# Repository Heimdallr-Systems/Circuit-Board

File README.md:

# Circuit-Board

Custom Power and IO board for the robot

## Folders

### CapsoneParts.3dshapes

Custom 3D models for KiCAD

### CapsstoneParts.pretty

Custom footprints for KiCAD

### optionalParts

Schematics of circuits that might be added to the main PCB

### Simulations/TINA-TI

[TINA-TI](https://www.ti.com/tool/TINA-TI) simulations used during design

### Simulations/LTspice

[LTspice](https://www.analog.com/en/design-center/design-tools-and-calculators/ltspice-simulator.html) simulations used
during design process

### TPS55288RPMR

Files used to make the TPS55288 components for KiCAD

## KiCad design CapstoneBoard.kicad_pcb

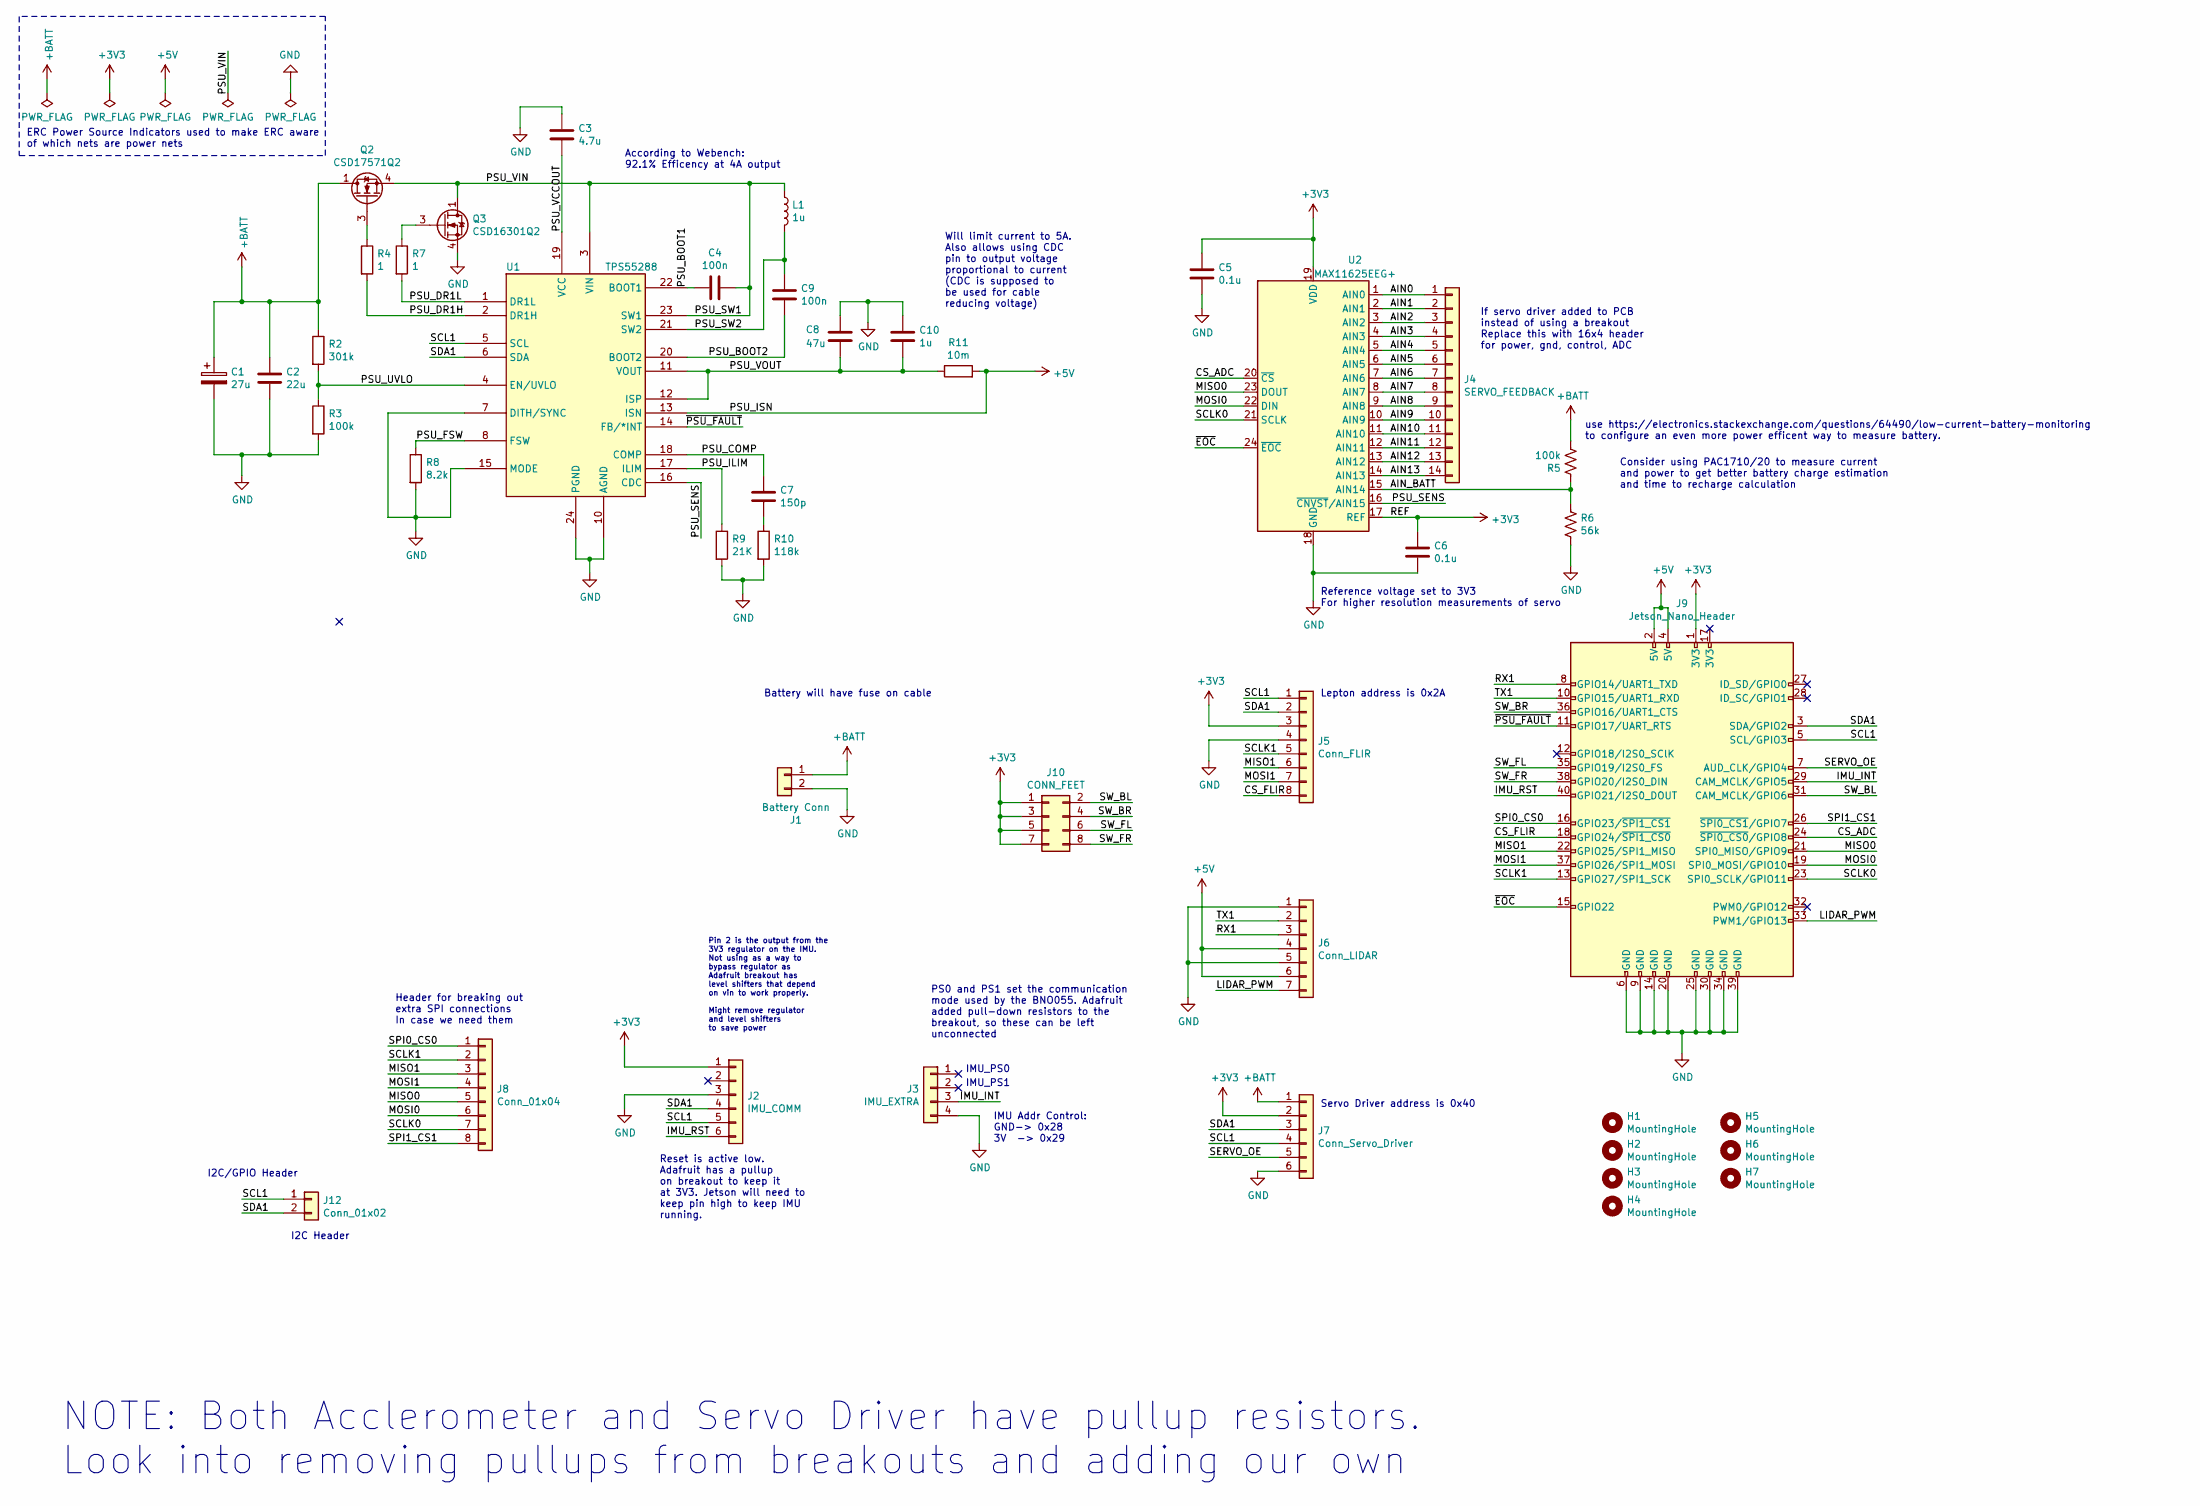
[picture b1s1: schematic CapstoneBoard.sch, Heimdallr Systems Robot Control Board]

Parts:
C1: 27u; C_1206_3216Metric_Pad1.33x1.80mm_HandSolder
C2: 22u; C_1206_3216Metric_Pad1.33x1.80mm_HandSolder
C3: 4.7u; C_1206_3216Metric_Pad1.33x1.80mm_HandSolder
C4, C9: 100n; C_1206_3216Metric_Pad1.33x1.80mm_HandSolder
C5, C6: 0.1u; C_0805_2012Metric_Pad1.18x1.45mm_HandSolder
C7: 150p; C_1206_3216Metric_Pad1.33x1.80mm_HandSolder
C8: 47u; C_1206_3216Metric_Pad1.33x1.80mm_HandSolder
C10: 1u; C_1206_3216Metric_Pad1.33x1.80mm_HandSolder
H1, H2, H3, H4, H5, H6, H7: MountingHole; MountingHole_2.5mm_Pad
J1: Battery Conn; wireConn2
J2: IMU_COMM; PinSocket_1x06_P2.54mm_Vertical
J3: IMU_EXTRA; PinSocket_1x04_P2.54mm_Vertical
J4: SERVO_FEEDBACK; PinHeader_1x14_P2.54mm_Vertical
J5: Conn_FLIR; PinHeader_1x08_P2.54mm_Vertical
J6: Conn_LIDAR; PinHeader_1x07_P2.54mm_Vertical
J7: Conn_Servo_Driver; PinHeader_1x06_P2.54mm_Vertical
J8: Conn_01x04; PinHeader_1x08_P2.54mm_Vertical
J9: Jetson_Nano_Header; PinHeader_2x20_P2.54mm_Vertical
J10: CONN_FEET; PinHeader_2x04_P2.54mm_Vertical
J12: Conn_01x02; PinHeader_1x02_P2.54mm_Vertical
L1: 1u; L_Vishay_IHLP-1212
Q2: CSD17571Q2; Texas_DQK
Q3: CSD16301Q2; Texas_DQK
R2: 301k; R_1206_3216Metric_Pad1.30x1.75mm_HandSolder
R3, R5: 100k; R_1206_3216Metric_Pad1.30x1.75mm_HandSolder
R4, R7: 1; R_1206_3216Metric_Pad1.30x1.75mm_HandSolder
R6: 56k; R_1206_3216Metric_Pad1.30x1.75mm_HandSolder
R8: 8.2k; R_1206_3216Metric_Pad1.30x1.75mm_HandSolder
R9: 21K; R_1206_3216Metric_Pad1.30x1.75mm_HandSolder
R10: 118k; R_1206_3216Metric_Pad1.30x1.75mm_HandSolder
R11: 10m; R_1206_3216Metric_Pad1.30x1.75mm_HandSolder
U1: TPS55288; VQFN-HR-26
U2: MAX11625EEG+; QSOP-24_3.9x8.7mm_P0.635mm

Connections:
+3V3: C5.1, C6.1, J2.1, J5.3, J7.2, J9.1 (3V3), J10.1, J10.3, J10.5, J10.7, U2.17 (REF), U2.19 (VDD)
+5V: J6.4, J6.6, J9.2 (5V), J9.4 (5V), R11.2, U1.13 (ISN)
+BATT: C1.1, C2.1, J1.1, J7.1, Q2.1 (D), Q2.2 (D), Q2.5 (D), Q2.6 (D), Q2.8 (D), R2.1, R5.2
/AIN0: J4.1, U2.1 (AIN0)
/AIN1: J4.2, U2.2 (AIN1)
/AIN2: J4.3, U2.3 (AIN2)
/AIN3: J4.4, U2.4 (AIN3)
/AIN4: J4.5, U2.5 (AIN4)
/AIN5: J4.6, U2.6 (AIN5)
/AIN6: J4.7, U2.7 (AIN6)
/AIN7: J4.8, U2.8 (AIN7)
/AIN8: J4.9, U2.9 (AIN8)
/AIN9: J4.10, U2.10 (AIN9)
/AIN10: J4.11, U2.11 (AIN10)
/AIN11: J4.12, U2.12 (AIN11)
/AIN12: J4.13, U2.13 (AIN12)
/AIN13: J4.14, U2.14 (AIN13)
/AIN_BATT: R5.1, R6.1, U2.15 (AIN14)
/CS_ADC: J9.24 (~SPI0_CS0~/GPIO8), U2.20 (~CS)
/CS_FLIR: J5.8, J9.18 (GPIO24/~SPI1_CS0~)
/IMU_INT: J3.3, J9.29 (CAM_MCLK/GPIO5)
/IMU_RST: J2.6, J9.40 (GPIO21/I2S0_DOUT)
/LIDAR_PWM: J6.7, J9.33 (PWM1/GPIO13)
/MISO0: J8.5, J9.21 (SPI0_MISO/GPIO9), U2.23 (DOUT)
/MISO1: J5.6, J8.3, J9.22 (GPIO25/SPI1_MISO)
/MOSI0: J8.6, J9.19 (SPI0_MOSI/GPIO10), U2.22 (DIN)
/MOSI1: J5.7, J8.4, J9.37 (GPIO26/SPI1_MOSI)
/PSU_BOOT1: C4.2, U1.22 (BOOT1)
/PSU_BOOT2: C9.1, U1.20 (BOOT2)
/PSU_COMP: C7.1, U1.18 (COMP)
/PSU_DR1H: R4.2, U1.2 (DR1H)
/PSU_DR1L: R7.2, U1.1 (DR1L)
/PSU_FSW: R8.1, U1.8 (FSW)
/PSU_ILIM: R9.1, U1.17 (ILIM)
/PSU_SENS: U1.16 (CDC), U2.16 (~CNVST~/AIN15)
/PSU_SW1: C4.1, L1.1, Q2.4 (S), Q2.7 (S), Q3.1 (D), Q3.2 (D), Q3.5 (D), Q3.6 (D), Q3.8 (D), U1.3 (VIN), U1.23 (SW1)
/PSU_SW2: C9.2, L1.2, U1.21 (SW2), U1.25 (SW2)
/PSU_UVLO: R2.2, R3.1, U1.4 (EN/UVLO)
/PSU_VCCOUT: C3.2, U1.19 (VCC)
/PSU_VOUT: C8.2, C10.2, R11.1, U1.11 (VOUT), U1.12 (ISP), U1.26 (VOUT)
/RX1: J6.3, J9.8 (GPIO14/UART1_TXD)
/SCL1: J2.5, J5.1, J7.4, J9.5 (SCL/GPIO3), J12.1, U1.5 (SCL)
/SCLK0: J8.7, J9.23 (SPI0_SCLK/GPIO11), U2.21 (SCLK)
/SCLK1: J5.5, J8.2, J9.13 (GPIO27/SPI1_SCK)
/SDA1: J2.4, J5.2, J7.3, J9.3 (SDA/GPIO2), J12.2, U1.6 (SDA)
/SERVO_OE: J7.5, J9.7 (AUD_CLK/GPIO4)
/SPI0_CS0: J8.1, J9.16 (GPIO23/~SPI1_CS1~)
/SPI1_CS1: J8.8, J9.26 (~SPI0_CS1~/GPIO7)
/SW_BL: J9.31 (CAM_MCLK/GPIO6), J10.2
/SW_BR: J9.36 (GPIO16/UART1_CTS), J10.4
/SW_FL: J9.35 (GPIO19/I2S0_FS), J10.6
/SW_FR: J9.38 (GPIO20/I2S0_DIN), J10.8
/TX1: J6.2, J9.10 (GPIO15/UART1_RXD)
/~EOC~: J9.15 (GPIO22), U2.24 (~EOC)
/~PSU_FAULT~: J9.11 (GPIO17/UART_RTS), U1.14 (FB/*INT)
GND: C1.2, C2.2, C3.1, C5.2, C6.2, C8.1, C10.1, J1.2, J2.3, J3.4, J5.4, J6.1, J6.5, J7.6, J9.6 (GND), J9.9 (GND), J9.14 (GND), J9.20 (GND), J9.25 (GND), J9.30 (GND), J9.34 (GND), J9.39 (GND), Q3.4 (S), Q3.7 (S), R3.2, R6.2, R8.2, R9.2, R10.2, U1.7 (DITH/SYNC), U1.9 (PGND), U1.10 (AGND), U1.15 (MODE), U1.24 (PGND), U2.18 (GND)
unnamed: C7.2, R10.1
unnamed: Q2.3 (G), R4.1
unnamed: Q3.3 (G), R7.1

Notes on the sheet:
Lepton address is 0x2A
NOTE: Both Acclerometer and Servo Driver have pullup resistors. Look into removing pullups from breakouts and adding our own
Servo Driver address is 0x40
Reset is active low. Adafruit has a pullup on breakout to keep it at 3V3. Jetson will need to keep pin high to keep IMU running.
IMU_PS0
IMU_PS1
IMU Addr Control: GND-> 0x28 3V -> 0x29
PS0 and PS1 set the communication mode used by the BNO055. Adafruit added pull-down resistors to the breakout, so these can be left unconnected
Pin 2 is the output from the 3V3 regulator on the IMU. Not using as a way to bypass regulator as Adafruit breakout has level shifters that depend on vin to work properly. Might remove regulator and level shifters to save power
Reference voltage set to 3V3 For higher resolution measurements of servo
ERC Power Source Indicators used to make ERC aware of which nets are power nets
Battery will have fuse on cable
According to Webench: 92.1% Efficency at 4A output
Will limit current to 5A. Also allows using CDC pin to output voltage proportional to current (CDC is supposed to be used for cable reducing voltage)
Header for breaking out extra SPI connections In case we need them
Consider using PAC1710/20 to measure current and power to get better battery charge estimation and time to recharge calculation
use https://electronics.stackexchange.com/questions/64490/low-current-battery-monitoring to configure an even more power efficent way to measure battery.
If servo driver added to PCB instead of using a breakout Replace this with 16x4 header for power, gnd, control, ADC
I2C/GPIO Header
I2C Header

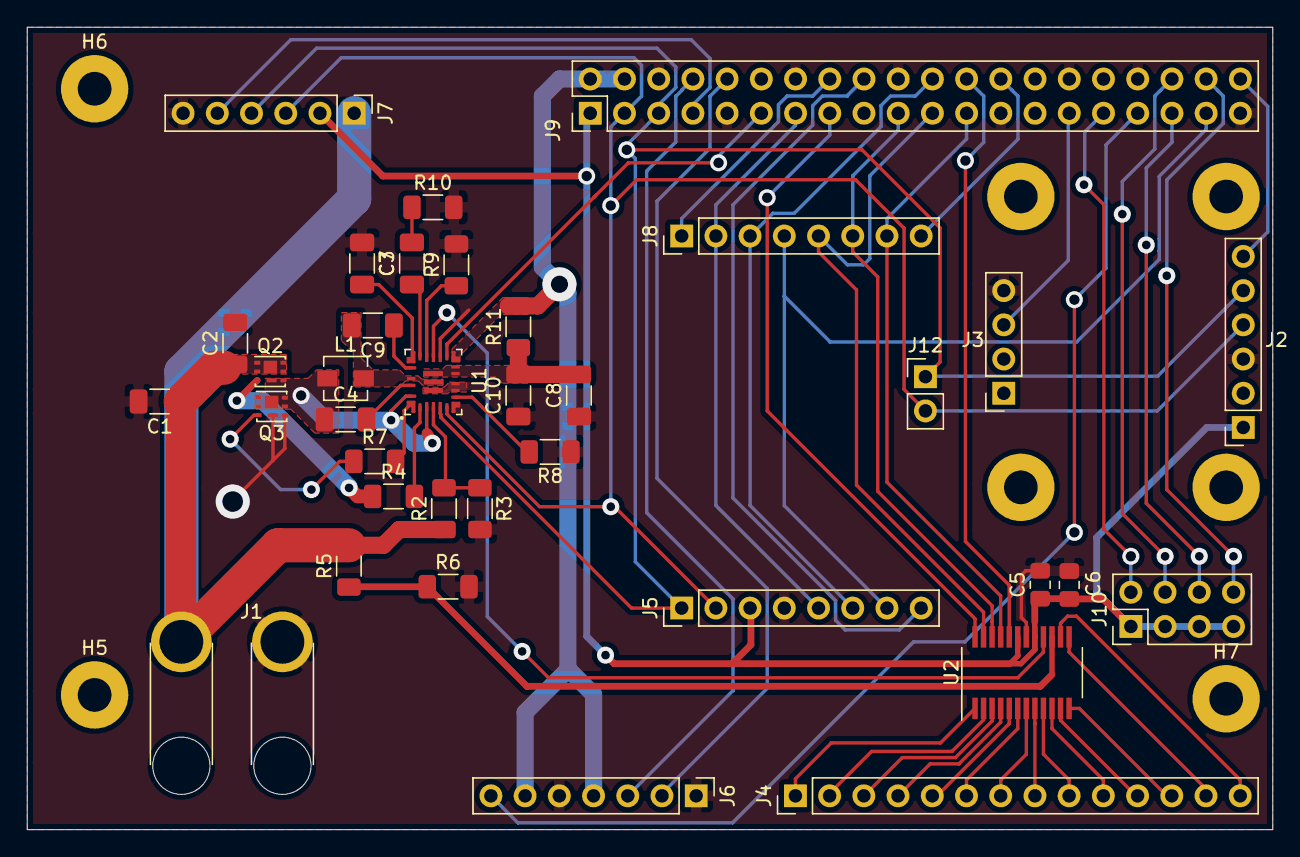
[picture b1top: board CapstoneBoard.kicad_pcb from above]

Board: 2 copper layers, 92.5 x 59.6 mm, 43 parts (0 on the bottom side), 59 nets.

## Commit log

2021-02-13 Add project files
2021-02-16 PCB Rev 3
2021-02-26 Revision 3 completed
2021-03-22 Update board for better soldering without plated drills.
